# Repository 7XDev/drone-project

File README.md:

# Drones

The repository for the [ESP 32 Drones](https://www.alibaba.com/product-detail/ESP-Drone-Quadcopter-DIY-Educational-Learning_1600878049371.html) with software set up already and ready to go.

Find the official documentation [here](https://docs.espressif.com/projects/espressif-esp-drone/en/latest/gettingstarted.html#esp-drone-overview)

## Dependencies

This project is using a modified version of following repositories
 - [leeebo's cfclient](https://github.com/leeebo/crazyflie-clients-python)
 - [espressif's esp drone](https://github.com/espressif/esp-drone)

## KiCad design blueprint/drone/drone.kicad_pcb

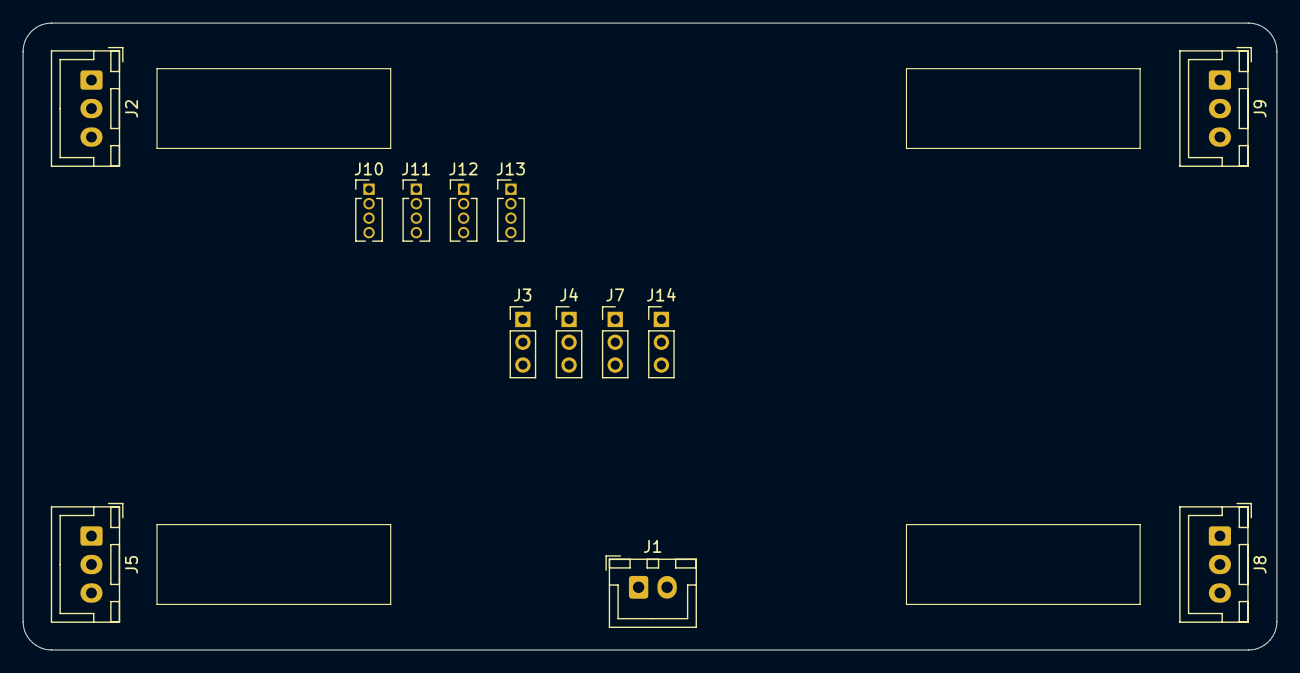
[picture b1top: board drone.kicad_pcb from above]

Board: 2 copper layers, 110.0 x 55.0 mm, 13 parts (0 on the bottom side), 14 nets, no tracks yet.

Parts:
J1: Connector battery; JST_XH_B2B-XH-A_1x02_P2.50mm_Vertical
J2: Motor 1 IN; JST_XH_B3B-XH-A_1x03_P2.50mm_Vertical
J3, J4, J7, J14: ESC 0 OUT; PinHeader_1x03_P2.00mm_Vertical
J5: Motor 2 IN; JST_XH_B3B-XH-A_1x03_P2.50mm_Vertical
J8: Motor 3 IN; JST_XH_B3B-XH-A_1x03_P2.50mm_Vertical
J9: Motor 0 IN; JST_XH_B3B-XH-A_1x03_P2.50mm_Vertical
J10, J11, J12, J13: ESC 0 IN; PinHeader_1x04_P1.27mm_Vertical

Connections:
unnamed: J1.1, J10.4, J11.4, J12.4, J13.4
unnamed: J1.2, J10.3, J11.3, J12.3, J13.3
unnamed: J2.1, J7.3
unnamed: J2.2, J7.2
unnamed: J2.3, J7.1
unnamed: J3.1, J5.3
unnamed: J3.2, J5.2
unnamed: J3.3, J5.1
unnamed: J4.1, J8.3
unnamed: J4.2, J8.2
unnamed: J4.3, J8.1
unnamed: J9.3, J14.1
unnamed: J9.2, J14.2
unnamed: J9.1, J14.3

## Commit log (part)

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2025-11-04 Added README.md underlining the simple file
2025-11-04 Renamed md file to now be sperate for the layout of the page
2025-11-04 Added new content.md file and made minor changes to fit the new sperate file style
2025-11-04 Added assembly category for content.md
2025-11-04 Added proramming category for content.md
2025-11-04 Initial plan
2025-11-04 Add comprehensive guide for managing collaborator permissions
2025-11-04 Improved structure by adding a doc folder and added project-description.md
2025-11-04 Changed structure part of project-description.md
2025-11-05 Added initial md to html converter test
2025-11-05 Added basic function placeholder for md-converter.js
2025-11-05 Implemented converter and added simple showcase html
2025-11-05 Added stylesheet for converted md text
2025-11-05 Added code block support for md-converter
2025-11-05 Added assets folder with fonts
2025-11-05 Moved assets folder under src, Added font league-spartan, Created credits.txt, Added image for the header
2025-11-05 Added markdown-styles.css to src and added folder scripts to src with md-converter.js
2025-11-05 Added basic structure to implement content browser
2025-11-05 Added place´holder functions to content-browser.js
2025-11-05 Added styles folder
2025-11-05 Changed path of fonts in styles.css
2025-11-05 Optimized layout main page
2025-11-05 Added basic content browser showcase
2025-11-05 Added loading of topic category titles
2025-11-05 Fixed path of script.js
2025-11-05 Update project description with a new special feature
    Added a new feature description for the online coding-IDE.
2025-11-06 Added item structure of content-browser.js
2025-11-07 Remove typo 's'
2025-11-07 Added favicon
2025-11-07 Removed placeholders for topics in index.html
2025-11-07 Changed emojis in content-structure.json, Fixed gap in topic-selector
2025-11-07 Added JS logic to select the first topic-button on load
2025-11-07 Fixed content-browser.js class names, Fixed styles for topic-category-button
2025-11-07 Added JS logic for selecting/unselecting and toggling/detoggling topic-category-buttons
2025-11-07 Added arrow logic in JS for topic-category-button
2025-11-07 Added svg icon for the topic-category-button instead of the unicode text.
2025-11-07 Added missing icon credit and added documentation in content-browser.js
2025-11-07 Fixed very confusing variable definition in script.js
2025-11-07 Fixed visibility issue with content-browser.js
2025-11-07 Fixed major performance issue with O=n^2 with now O=1 and restructured script.js
2025-11-07 Applied basic fix for the category buttons not working as expected
2025-11-07 Outlined more changes in TODO.md
2025-11-08 Change toggle deToggle structure to refresh the DOM before calling the animation
2025-11-10 Made changes in script.js to find fix for transition issue for arrows
2025-11-10 Added isCaregoryButton check to JS
2025-11-10 Added styles for topic-under-category
2025-11-10 Moved the arrow-svg to the left
2025-11-10 Changed TODO.md
2025-11-10 Fixed util md-converter showcase
2025-11-10 Fixed sideline for children under category-topic-button
2025-11-10 Added basic animations to topic-category-button open/close
2025-11-10 Added linking and custom button functionality to md-converter.js
2025-11-10 Added handling of custom signatures for positive and negative boxes as well as warnings
2025-11-11 Added head and body support for warnings, positive, negative and warning blocks in md-converter.js
2025-11-11 Added table support for md-converter.js
2025-11-11 Added documentation for md-converter.js
2025-11-11 Fixed double-click issue for arrows in nav
2025-11-11 Added missing link to markdown styles
2025-11-11 Added template for markdown-loading
2025-11-11 Implemented markdown displaying in index.html
2025-11-11 Added gap between topic-buttons and scrollbar
2025-11-11 Added alternative text to Drone Logo(index.html)
2025-11-11 Added div right-panel-header
2025-11-11 Fixed category loading issue
2025-11-11 Fixed missing arrow animations for categories with path and issue where pop in animations applied to all children of all elements
2025-11-11 Added Right-Panel-Bar
2025-11-11 Fixed opening bug for categories with paths
2025-11-11 Added RightPanel support for first-site-load
2025-11-11 Added welcome page in content
2025-11-11 Added software list document
2025-11-11 Removed tmp TODO.md.html file
2025-11-17 Show inital topic on site load
2025-11-17 Added smooth effect to scrolling for right-panel and fixed issue that header gets smaller
2025-11-17 Added new todo in TODO.md
2025-11-17 Changed TODO.md and migrated TODOs for Markus into GitHub issues
2025-11-17 Added Copy button
2025-11-17 Synced markdown-styles.css between showcase and src
2025-11-17 Changed software-list.md to use ` ` instead of embedded html
2025-11-17 Fixed Copy button position
2025-11-17 Fixed issue with previously improved function
2025-11-17 Improved structure and added more documentation in script.js
2025-11-17 Improved Dark-mode styles
2025-11-17 Added first step of issue #3
2025-11-18 Finished issue #3
2025-11-18 Added detection for button in md-converter.js
2025-11-18 Added basic button support for md-converter.js
2025-11-18 Synced markdown converter script and style from util to src
2025-11-19 Implemented basic budget.md layout
2025-11-19 Added budget.md content
2025-11-19 General parts-list category overhaul
2025-11-19 Added safety-legal.md content
2025-11-20 Fished all content within prequisites category
2025-11-20 Added #end tag to md-converter.js
2025-11-20 Added .prettierrc and settings.json
2025-11-21 Add website layout section to README
    Added a section for the website layout with an image.
2025-11-24 Synced src markdown converter to util markdown converter
2025-11-24 Resolved issues with renaming the initial page
2025-11-24 Fixed os issue with regex matching for markdown header detection
2025-11-25 Synced util markdown converter with the src markdown converter
2025-11-25 Removed util directory to deal with merge issues
2025-11-25 Called flatstructure function in the constructor of the content browser in script.js
2025-11-25 Added Icons to copyButton and to lightDarkModeToggleButton
2025-11-25 Changed convert signature of md-converter.js and implemented new signature in script.js
2025-11-26 Reworked end item generation to check if it is the first or last item and generate the HTML item accordingly
2025-11-26 Added end tag to each markdown content file
2025-11-26 Added basic functionality for the end tags
2025-11-26 Fixed end tag navigation issue where you couldn't use them after selecting a topic in the topic selector
2025-11-28 Moved image from README.md to procject-description.md
2025-11-28 Rebranding of README.md
2025-11-28 Added comment in script.js to have changes to commit to new feature branch
2025-11-28 Reworked layout.md and the milestones and moved them to the project description
2025-12-01 Fixed Icon-sizing for copybutton & Dark/Light mode button
2025-12-01 Added icons to markdown-signature-blocks
2025-12-01 Improved Dark-Mode text colors
2025-12-01 Finished credits.html page
2025-12-01 Improved #end button animations
2025-12-01 Improved dark-mode colors for #end button
2025-12-01 Added AI focus in introduction.md
2025-12-01 Fixed scaling issue with the icons for mode switch and copy
2025-12-01 Improved dark-mode styles for #end button border
2025-12-01 Fixed path of warning-signature-block icon
2025-12-01 Updated cancel.svg and added to path of negative-box
2025-12-01 Fixed typo in styles.css
2025-12-01 Started rework on parts-list.md
2025-12-01 Enchanced credits.html to use markdown-files to render content
2025-12-01 Added help.html
2025-12-01 Added Base for help.md
2025-12-01 Fixed light/dark-mode issue when switching html files
2025-12-01 Implemented logic to automatically scroll to top if #end button clicked
2025-12-01 Update image in README.md for website layout
2025-12-02 REworked introduction.md
2025-12-02 Reworked index.html to improve lighthouse statistics
2025-12-02 Added local saving of current page and open / close state of pages in local storage
2025-12-02 Reworked project-descripition.md to match the new direction of the project
2025-12-02 Moved information from doc/md-converter.md into help.md
2025-12-02 Added arrow icons to #end button
2025-12-02 Moved content-structure.json to root directory of src/
2025-12-02 Added animations for icon previous #end button
2025-12-04 Fixed certain items mode switch transition
2025-12-04 Removed unnecessary end lines in all content .md files
2025-12-05 Added fadeOut animation to page items under category button
2025-12-05 Added html and styles for search bar
2025-12-05 Added base for mobile optimazation
2025-12-08 Added darkmode to searchbar popup
2025-12-08 Added animations to searchbar popup
2025-12-09 Reworked descriptions for the products in parts-list.md
2025-12-10 Finalized parts in parts-list.md
2025-12-10 Reworked parts-list.md
2025-12-10 Adapted budget.md according to the most recent changes
2025-12-10 Applied style changes #43
2025-12-10 Fixed transition #41
2025-12-10 Resolved merge issue and readded fix to #41
2025-12-10 Fixed mode switch button allignment in help.html and credits.html #47
2025-12-10 Removed trailing slashes on link tags in help.html and credits.html
2025-12-10 Implemented quick fix for #35
2025-12-10 Added .gitignore
2025-12-10 Finished #38
2025-12-11 Added preemtive splitting of src/ into src/doc/ and src/client/
2025-12-11 Reworked certain parts of content to match the new components
2025-12-11 Added src/tools/ with a new md converter showcase
2025-12-11 Fixed darkmode/lightmode button logic #49
2025-12-11 Removed unused showcase code comments
2025-12-11 Removed unused styles & renamed css rules
2025-12-11 Reworked js for searchbar & added logic to remove text on blur
2025-12-11 Moved fonts into src/assets/fonts/
2025-12-11 Finished search bar | #30
2025-12-12 Added content to exploring-components.md
2025-12-12 Minor styles.css fix
2025-12-12 MInor md-converter.js improvments
2025-12-12 Improved formatted code block implementation and added basic style
2025-12-12 Added line numbering support for formatted code blocks
2025-12-12 Added copy support for formatted code blocks #51
2025-12-12 Implemented method for basic color formatting of c / c++ code #51
2025-12-13 Applied style fix for #55
2025-12-13 Applied fix for #54 and started coloring code based on css classes
2025-12-13 Added style for quitation marks (qmarks) and applied fix for #54
2025-12-13 Added recoginition for brackets #51
2025-12-13 ADded recoginition for objects and properties #51
2025-12-13 Added .prettierrc and settings.json #53
2025-12-13 Reworked .prettierrc #53
2025-12-13 Appplied .prettierrc styling on all relevant files
2025-12-15 Added new Performance Metrics page
2025-12-15 Improved margin-left for topic-selector
2025-12-15 Mobile Optimazation: Remove right-hand-panel bar
2025-12-15 Mobile Optimazation: Made max-width
2025-12-15 Mobile Optimazation: Finished Searchbar
2025-12-15 Finished power usage for battery powered devices and sensors
2025-12-15 Mobile Optimazation: Some more changes
2025-12-15 Mobile Optimazation: End buttons
2025-12-15 Mobile Optimazation: Some header changes
2025-12-15 Mobile Optimazation: Scrolling inside markdown-elements
2025-12-15 Some Performance optimazations
2025-12-16 Added pcb project for the drone
2025-12-16 Fixed typo in parts-list.md
2025-12-16 Added basic implementation of battery connection and esc to motor connection in the pcb
2025-12-16 Fixed tables on desktop viewport
2025-12-16 Updated pcb design
2026-02-10 Replaced submodules with attribution
2026-02-10 Added 3d model for drone props
2026-02-26 Merged files into main branch
2026-03-07 Added web panel repository
2026-04-13 Add .gitattributes to mark .gcode as generated
2026-04-13 Removed web directory from main branch
2026-04-13 Added drone client with wasd/controller support
2026-04-13 Added option to use GPU for depth mapping
2026-04-13 Added output showing how long mapping took
2026-04-13 Added options to input performance parameters
2026-04-14 Some updates
2026-04-14 Updated reference images for demo
2026-05-05 Updated Makefile, Agents.md & Emergency_stop_timeout reduced
2026-05-05 Fixed Firmware
2026-06-09 Added Multi-Drone support to firmware & controller_control
